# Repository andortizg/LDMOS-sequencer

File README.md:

# ATtiny85 TX/RX Sequencer for HF LDMOS Power Amplifier with overdrive protection

ATtiny85-based TX/RX sequencer for a 1KW HF LDMOS solid-state power amplifier. Provides safe relay sequencing, overdrive protection, and hardware watchdog supervision.

## Features

- Correct TX/RX relay sequencing to protect both the LDMOS transistor and the transceiver
- Overdrive input protection: blocks bias if input power exceeds threshold
- Hardware watchdog (250ms): returns to safe RX state if firmware hangs
- Fail-safe design: all relays return to bypass (RX) on power loss or STBY mode

## Hardware Integration

This sequencer is designed to work with the following boards:

- **SP6GK TX-RX Relay Board** — handles RF switching (RM85 relays), input SWR bridge, and overpower detection ([GitHub](https://github.com/SP6GK/TXRX_Relay_Board))
- **S21RC LDMOS SSPA Controller V2.1 Lite** — manages LDMOS bias, display, and secondary protections ([GitHub](https://github.com/s21rc/ldmos_sspa_controller_v2.1_lite))
- **DXWorld-e Protection Board** — hardware overcurrent, overvoltage, and VSWR protection via BTS50085 (30µs cutoff)

## Pin Mapping

| Pin | Arduino | Direction | Function |
|-----|---------|-----------|----------|
| PB0 | D0 | INPUT | OVERDRIVE — HIGH_PWR_IN from SP6GK board (active HIGH) |
| PB1 | D1 | OUTPUT | RF_RELAY_IN — TRX input relay via BC547→SP6GK PNP (HIGH=active) |
| PB2 | D2 | OUTPUT | PTT_OUT — PTT to S21RC controller (HIGH=TX, 12V) |
| PB3 | D3 | INPUT | PTT_IN — Operator PTT, active LOW (internal pull-up) |
| PB4 | D4 | OUTPUT | RF_RELAY_OUT — ANT output relay via BC547→SP6GK PNP (HIGH=active) |
| PB5 | — | — | RESET — do not use |

## TX Sequence

```
1. ANT output relay → TX     (no RF load, bias off)
2. Wait 10ms
3. TRX input relay  → TX
4. Wait 10ms
5. PTT_OUT → HIGH            (S21RC activates bias, keys transceiver)
6. Wait 15ms                 (bias stabilization margin)
→ RF active
```

## RX Sequence

```
1. PTT_OUT → LOW             (S21RC cuts bias, stops transceiver)
2. Wait 8ms                  (RF decay)
3. TRX input relay  → RX
4. Wait 10ms
5. ANT output relay → RX
```

## Overdrive Protection

The SP6GK board includes an overpower detector with adjustable threshold (via potentiometer) that drives the HIGH_PWR_IN signal HIGH when input power exceeds the set level.

When overdrive is detected during TX:

1. PTT_OUT is pulled LOW immediately
2. S21RC interprets this as end of TX and cuts LDMOS bias
3. RF relays remain in TX position (operator still holds PTT)
4. **Bias is not restored until the operator releases PTT** (manual reset required)

## STBY/OPER Switch

A normally-closed switch in series with PTT_IN provides STBY mode entirely in hardware:

- **OPER**: switch closed → normal operation
- **STBY**: switch open → PTT_IN never goes LOW → no TX sequence, bias never activated
- Relay coil power is also cut in STBY → RM85 relays return to NC (bypass) → antenna connected directly to transceiver

This is a fully fail-safe design: cable break or switch failure defaults to STBY/bypass.

## Bias Relay

The LDMOS gate bias line is switched by a dedicated relay controlled by the S21RC controller. The relay coil current is negligible (LDMOS gate is capacitive, leakage in µA range). A small signal relay (SRD-12VDC, HK19F, etc.) is sufficient.

The relay driver uses a BC547 NPN transistor in common-emitter configuration driven by PTT_OUT via the S21RC controller output, providing full galvanic isolation between the control circuitry and the LDMOS gate bias network.

## Watchdog

The ATtiny85 internal watchdog is enabled with a 250ms timeout. If the firmware hangs for any reason, the micro resets and `setup()` immediately drives all outputs to the safe RX state:

```
RF_RELAY_OUT → LOW  (ANT relay to bypass)
RF_RELAY_IN  → LOW  (TRX relay to bypass)
PTT_OUT      → LOW  (S21RC in RX, bias off)
```

## Requirements

- **Arduino IDE** with ATtiny85 board support ([ATTinyCore](https://github.com/SpenceKonde/ATTinyCore) recommended)
- **Clock**: 8MHz internal oscillator (no external crystal needed)
- **Fuses**: default — do not burn RSTDISBL (PB5/RESET must remain as reset pin)

## Programming

Use any ISP programmer (USBasp, Arduino as ISP) via the SPI header on PB0/PB1/PB2/PB5.

Board settings in Arduino IDE:
```
Board:     ATtiny85
Clock:     8 MHz (internal)
Programmer: USBasp (or Arduino as ISP)
```

## License

MIT License — feel free to use and modify for your own amplifier builds.

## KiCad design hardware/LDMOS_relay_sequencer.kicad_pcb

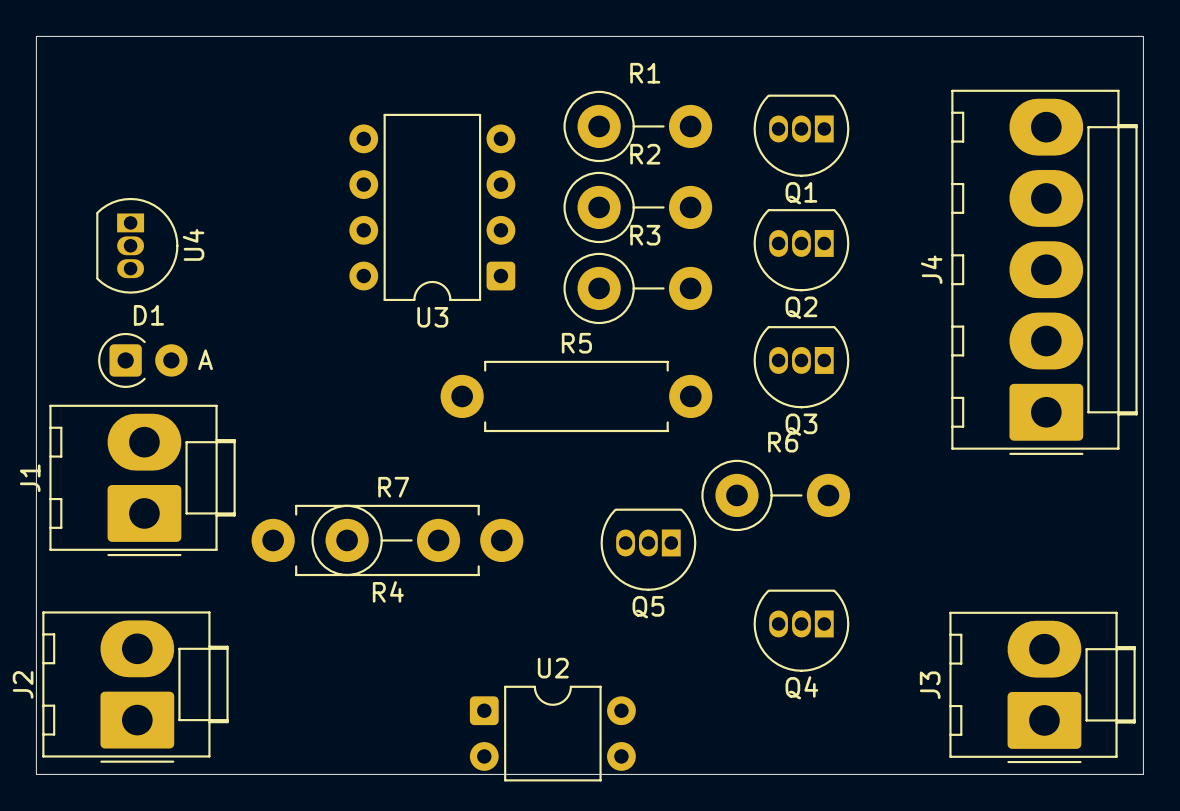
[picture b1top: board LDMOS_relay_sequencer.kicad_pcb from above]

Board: 2 copper layers, 61.5 x 41.0 mm, 20 parts (0 on the bottom side), 22 nets, no tracks yet.

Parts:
D1: 1N4001; D_A-405_P2.54mm_Vertical_AnodeUp
J1, J2, J3: Conn_01x02_Pin; Molex_KK-396_A-41791-0002_1x02_P3.96mm_Vertical
J4: Conn_01x05_Pin; Molex_KK-396_A-41791-0005_1x05_P3.96mm_Vertical
Q1, Q2, Q3, Q5: BC547; TO-92_Inline
Q4: BC557; TO-92_Inline
R1, R2, R3, R6: 1K; R_Axial_DIN0411_L9.9mm_D3.6mm_P5.08mm_Vertical
R4: 1K8; R_Axial_DIN0411_L9.9mm_D3.6mm_P12.70mm_Horizontal
R5: 1K; R_Axial_DIN0411_L9.9mm_D3.6mm_P12.70mm_Horizontal
R7: 10K; R_Axial_DIN0411_L9.9mm_D3.6mm_P5.08mm_Vertical
U2: PC817; DIP-4_W7.62mm
U3: ATtiny85-20P; DIP-8_W7.62mm
U4: L78L05_TO92; TO-92_Inline

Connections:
GND: J1.2, J2.2, J3.2, J4.5, Q1.3 (E), Q2.3 (E), Q3.3 (E), Q5.3 (E), U3.4 (GND), U4.2 (GND)
unnamed: D1.1 (K), U4.3 (VI)
unnamed: J2.1, R6.1, U2.2
unnamed: J3.1, U2.3
unnamed: J4.1, R5.2
unnamed: J4.2, Q3.1 (C)
unnamed: J4.3, Q2.1 (C)
unnamed: J4.4, Q1.1 (C)
unnamed: Q1.2 (B), R1.2
unnamed: Q2.2 (B), R2.2
unnamed: Q3.2 (B), R3.2
unnamed: Q4.2 (B), R6.2
unnamed: Q4.1 (C), U3.3 (XTAL2/PB4)
unnamed: Q5.2 (B), R5.1
unnamed: Q5.1 (C), U3.2 (XTAL1/PB3)
unnamed: R4.1, U2.1
unnamed: R1.1, U3.5 (AREF/PB0)
unnamed: R2.1, U3.6 (PB1)
unnamed: R3.1, U3.7 (PB2)
unnamed: R7.1, U3.1 (~RESET/PB5)
VCC_5: Q4.3 (E), R7.2, U3.8 (VCC), U4.1 (VO)
VCC_12: D1.2 (A), J1.1, R4.2, U2.4

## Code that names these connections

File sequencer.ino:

#include <avr/wdt.h>

// TX/RX Sequencer for 1KW HF LDMOS Power Amplifier - ATtiny85
//
// Pin mapping:
// PB0 (pin5) - OVERDRIVE   : HIGH_PWR_IN from SP6GK TX-RX board, active HIGH
// PB1 (pin6) - RF_RELAY_IN : Input relay (TRX side) via BC547→PNP SP6GK (HIGH=active)
// PB2 (pin7) - PTT_OUT     : PTT signal to S21RC controller (HIGH=TX, 12V)
// PB3 (pin2) - PTT_IN      : Operator PTT input, active LOW (internal pull-up)
//                            Wired in series with STBY/OPER switch (NC=OPER)
// PB4 (pin3) - RF_RELAY_OUT: Output relay (ANT side) via BC547→PNP SP6GK (HIGH=active)
// PB5        - RESET, do not use
//
// Notes:
// - RF_RELAY_IN and RF_RELAY_OUT drive BC547 NPN transistors in common-emitter config
//   which pull the base of PNP drivers on the SP6GK board to GND, activating the RM85 relays
// - PTT_OUT drives the S21RC SSPA controller bias line (12V = TX active)
//   The S21RC controller activates the LDMOS bias and keys the transceiver
// - In STBY position, the STBY/OPER switch opens the PTT_IN line → micro never sees TX
//   and relay coil power is cut → RM85 relays return to NC (bypass) position
// - Overdrive protection (from SP6GK overpower detector) blocks PTT_OUT to S21RC
//   which interprets it as end of TX and cuts the LDMOS bias
//   Bias is NOT restored until operator releases PTT (manual reset required)
// - Hardware watchdog (250ms) resets the micro if firmware hangs,
//   returning all outputs to safe RX state via setup() initialization

#define OVERDRIVE    0
#define RF_RELAY_IN  1
#define PTT_OUT      2
#define PTT_IN       3
#define RF_RELAY_OUT 4

// Sequence timing in ms
#define T_RELAY     10   // RM85 mechanical relay switching time
#define T_BIAS      15   // margin for S21RC bias stabilization
#define T_RF_DECAY   8   // RF decay time after transceiver stops transmitting

bool inTX       = false;
bool biasKilled = false;  // true if PTT blocked due to overdrive protection

void setup() {
  wdt_disable();

  pinMode(OVERDRIVE,    INPUT);
  pinMode(RF_RELAY_IN,  OUTPUT);
  pinMode(PTT_OUT,      OUTPUT);
  pinMode(PTT_IN,       INPUT_PULLUP);
  pinMode(RF_RELAY_OUT, OUTPUT);

  // Safe initial state: RX
  // SP6GK relays in NC (bypass) position when BC547 is OFF
  digitalWrite(RF_RELAY_OUT, LOW);
  digitalWrite(RF_RELAY_IN,  LOW);
  digitalWrite(PTT_OUT,      LOW);  // LOW = S21RC in RX mode, bias OFF

  wdt_enable(WDTO_250MS);
}

// TX sequence:
//   1. ANT output relay switches to TX (no RF load, bias off)
//   2. TRX input relay switches to TX
//   3. PTT sent to S21RC (activates bias and keys transceiver)
void goTX() {
  digitalWrite(RF_RELAY_OUT, HIGH);
  delay(T_RELAY);
  wdt_reset();

  digitalWrite(RF_RELAY_IN, HIGH);
  delay(T_RELAY);
  wdt_reset();

  digitalWrite(PTT_OUT, HIGH);   // S21RC activates bias and transmits
  delay(T_BIAS);
  wdt_reset();

  inTX       = true;
  biasKilled = false;
}

// RX sequence:
//   1. PTT to S21RC released (S21RC cuts bias and stops transceiver)
//   2. Wait for RF decay
//   3. TRX input relay returns to RX
//   4. ANT output relay returns to RX
void goRX() {
  digitalWrite(PTT_OUT, LOW);    // S21RC cuts bias and stops transceiver
  delay(T_RF_DECAY);
  wdt_reset();

  digitalWrite(RF_RELAY_IN, LOW);
  delay(T_RELAY);
  wdt_reset();

  digitalWrite(RF_RELAY_OUT, LOW);

  inTX       = false;
  biasKilled = false;
}

// Overdrive protection: blocks PTT signal to S21RC
// S21RC interprets this as end of TX and cuts LDMOS bias
// Operator must release PTT to reset this condition
void killBias() {
  digitalWrite(PTT_OUT, LOW);
  biasKilled = true;
}

void loop() {
  wdt_reset();

  bool pttActive       = (digitalRead(PTT_IN)   == LOW);
  bool overdriveActive = (digitalRead(OVERDRIVE) == HIGH);

  // Overdrive protection: requires PTT release to reset
  if (inTX && overdriveActive && !biasKilled) {
    killBias();
  }

  // PTT management
  if (pttActive && !inTX) {
    goTX();
  } else if (!pttActive && inTX) {
    goRX();
  }
}
